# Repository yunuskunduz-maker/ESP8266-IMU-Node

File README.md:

# ESP8266 Wireless IMU Node (PCB Design) 📡

## 📋 Project Summary (Overview)

This project is a battery-powered, compact, and independent **Wireless Motion Sensor** node designed for **IoT (Internet of Things)** applications.

The board reads acceleration and gyroscope data through the onboard **MPU-6050** sensor and transmits it to a Wi-Fi network (MQTT, TCP/UDP, etc.) via the **ESP8266 (ESP-12F)** module. It features an internal **Boost Converter** circuit to allow operation from a single battery cell.

---

## 🛠️ Technical Specifications

| Feature | Detail |
| :--- | :--- |
| **Microcontroller** | ESP-12F (ESP8266 Wi-Fi SoC) |
| **Sensor** | MPU-6050 (3-Axis Accelerometer + 3-Axis Gyroscope) |
| **Power Source** | 1x AA or Li-Ion Battery Cell |
| **Power Management** | **MCP1640** Boost Converter (Generates 3.3V from 0.8V input) |
| **User Interface** | 1x Programmable Button, 2x Status LEDs |
| **Antenna** | On-board PCB antenna (Keep-out zone design applied) |
| **Design Tool** | KiCad EDA |

---

## 📸 Design Gallery

### 1. 3D Render
A 3D render of the final board assembly. The placement of the battery holder and the ESP module has been optimized for size.

### 2. PCB Layout & Routing
A dual-layer (2-Layer) design. "Keep-out" areas were strictly maintained in the RF (Antenna) section to ensure signal integrity. Power planes were kept wide to minimize electrical noise during transmission.

### 3. Schematic Diagram
The circuit schematic illustrating the power management stage and sensor connections.

---

## 🚀 Use Cases
* **Remote vibration analysis** (Machine health monitoring).
* **Wearable technologies** (Pedometer, fall detection).
* **Wireless sensor module** for robotics projects.
* **Smart home automation** triggers.

---

**License:** MIT License  
**Developer:** Yunus Kunduz

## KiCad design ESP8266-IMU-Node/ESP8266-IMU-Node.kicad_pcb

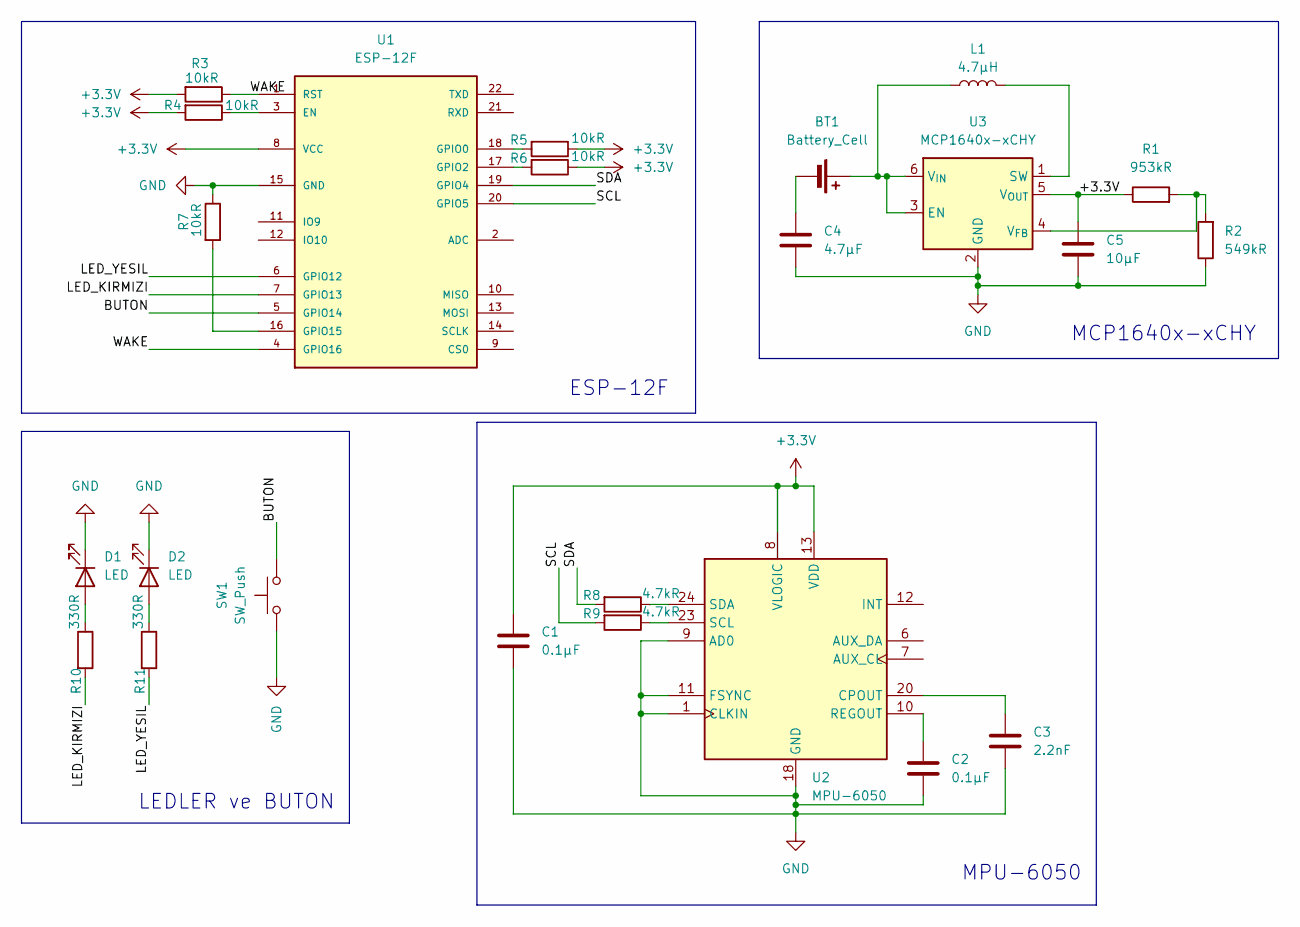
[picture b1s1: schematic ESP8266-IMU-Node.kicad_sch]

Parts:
BT1: Battery_Cell; BatteryHolder_Keystone_2466_1xAAA
C1, C2: 0.1μF; C_01005_0402Metric
C3: 2.2nF; C_01005_0402Metric
C4: 4.7μF; C_01005_0402Metric
C5: 10μF; C_01005_0402Metric
D1, D2: LED; LED_0805_2012Metric
L1: 4.7μH; L_1210_3225Metric
R1: 953kR; R_01005_0402Metric
R2: 549kR; R_01005_0402Metric
R3, R4, R5, R6, R7: 10kR; R_01005_0402Metric
R8, R9: 4.7kR; R_01005_0402Metric
R10, R11: 330R; R_01005_0402Metric
SW1: SW_Push; SW_PUSH_6mm
U1: ESP-12F; ESP-12E
U2: MPU-6050; InvenSense_QFN-24_4x4mm_P0.5mm
U3: MCP1640x-xCHY; SOT-23-6

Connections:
+3.3V: C1.1, C5.1, R1.1, R3.2, R4.2, R5.1, R6.1, U1.8 (VCC), U2.8 (VLOGIC), U2.13 (VDD), U3.5 (V_{OUT})
/BUTON: SW1.2, U1.5 (GPIO14)
/LED_KIRMIZI: R10.2, U1.7 (GPIO13)
/LED_YESIL: R11.2, U1.6 (GPIO12)
/SCL: R9.2, U1.20 (GPIO5)
/SDA: R8.2, U1.19 (GPIO4)
/WAKE: R3.1, U1.1 (RST), U1.4 (GPIO16)
GND: C1.2, C2.2, C3.2, C4.2, C5.2, D1.1 (K), D2.1 (K), R2.1, R7.1, SW1.1, U1.15 (GND), U2.1 (CLKIN), U2.9 (AD0), U2.11 (FSYNC), U2.18 (GND), U3.2 (GND)
unnamed: BT1.1 (+), L1.1, U3.3 (EN), U3.6 (V_{IN})
unnamed: BT1.2 (-), C4.1
unnamed: D1.2 (A), R10.1
unnamed: D2.2 (A), R11.1
unnamed: R4.1, U1.3 (EN)
unnamed: R5.2, U1.18 (GPIO0)
unnamed: R6.2, U1.17 (GPIO2)
unnamed: R7.2, U1.16 (GPIO15)
unnamed: C3.1, U2.20 (CPOUT)
unnamed: C2.1, U2.10 (REGOUT)
unnamed: R9.1, U2.23 (SCL)
unnamed: R8.1, U2.24 (SDA)
unnamed: L1.2, U3.1 (SW)
unnamed: R1.2, R2.2, U3.4 (V_{FB})

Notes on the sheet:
LEDLER ve BUTON
MPU-6050
MCP1640x-xCHY
ESP-12F

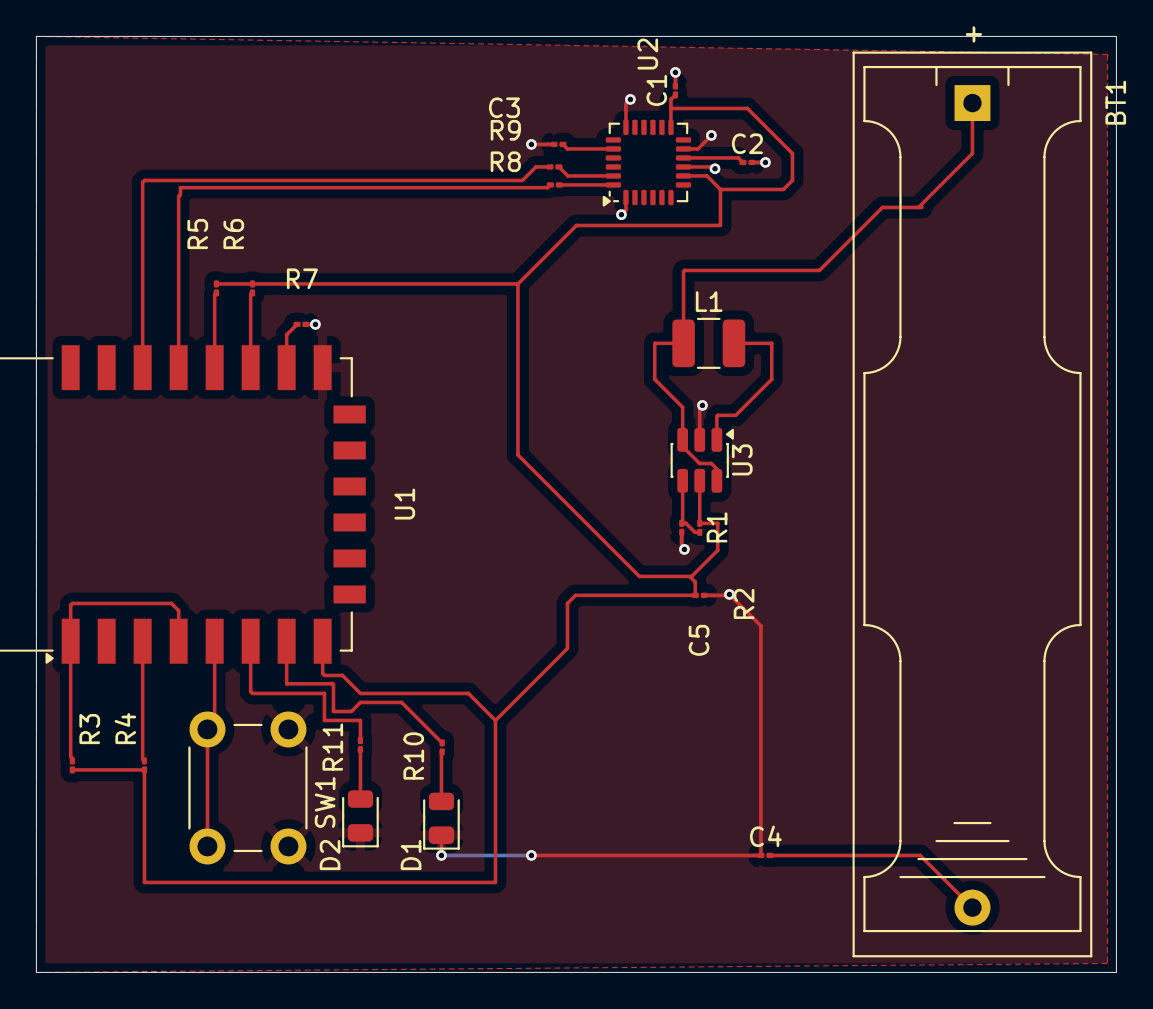
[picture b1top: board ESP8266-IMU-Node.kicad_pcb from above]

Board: 2 copper layers, 60.0 x 52.0 mm, 24 parts (0 on the bottom side), 22 nets.

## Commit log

2026-02-08 İlk Kurulum: ESP8266 IMU PCB Tasarımı
2026-02-08 resimler taşındı
2026-02-08 Add MIT License to the project
2026-02-09 Revise README for bilingual support and formatting
    Updated README.md to include English translations and improved formatting.
